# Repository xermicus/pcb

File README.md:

# Schemas and PCB
Shelter for my Schemas and PCB stuff

# LICENSE
This project is licensed under the [Mozilla Public License](LICENSE)

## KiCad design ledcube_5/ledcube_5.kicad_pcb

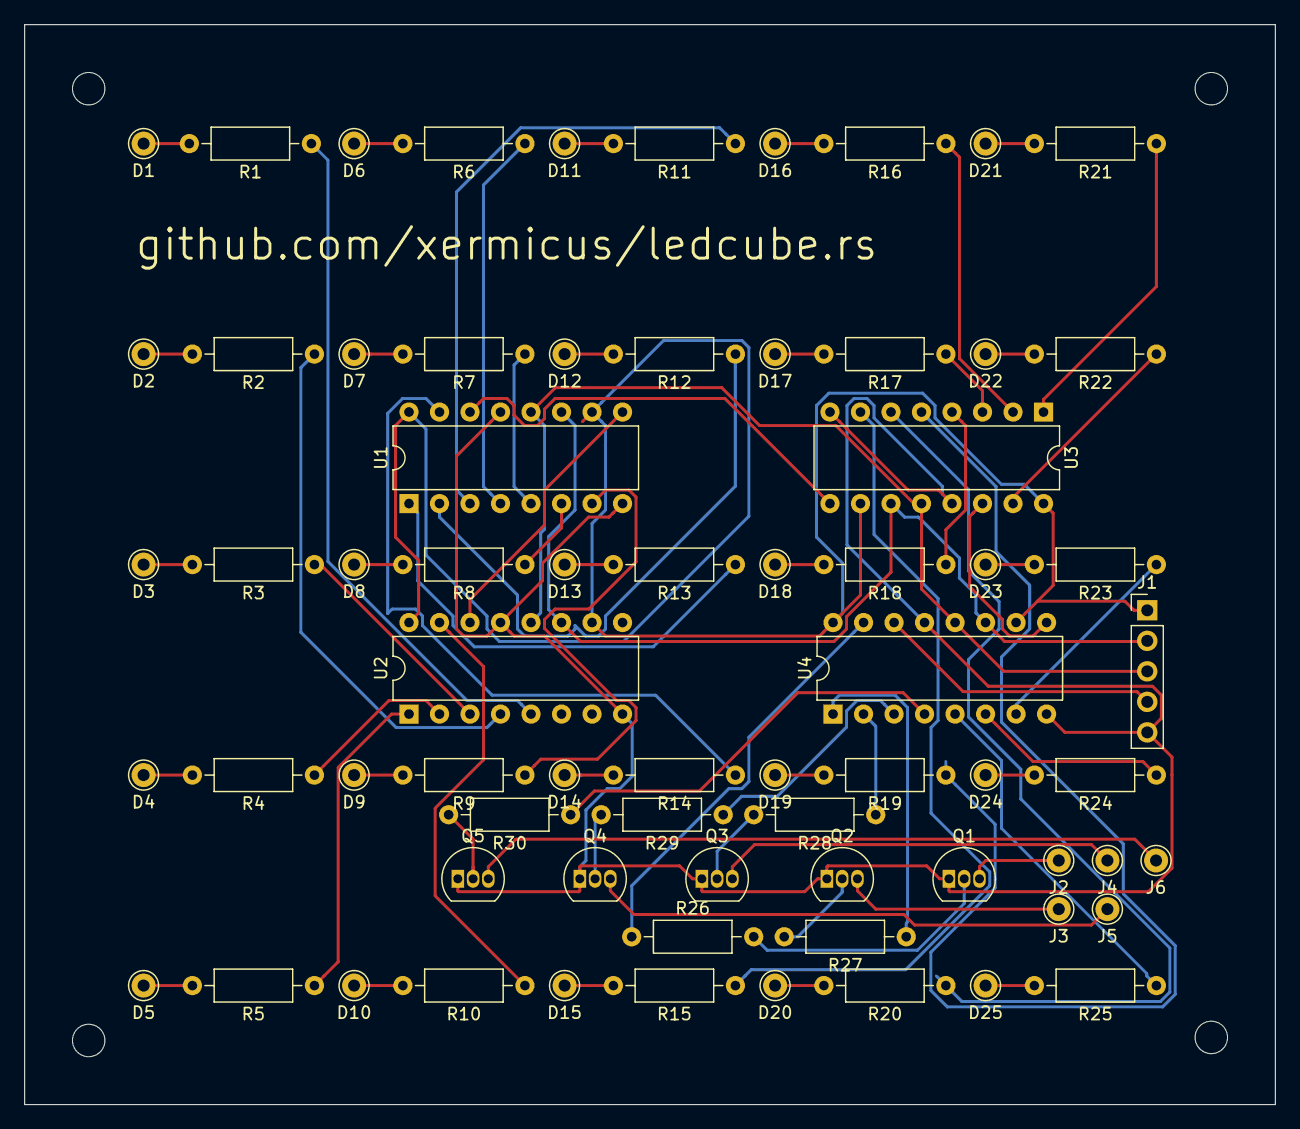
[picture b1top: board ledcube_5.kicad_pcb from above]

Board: 2 copper layers, 104.1 x 89.9 mm, 70 parts (0 on the bottom side), 73 nets.

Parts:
D1, D2, D3, D4, D5, D6, D7, D8, D9, D10, D11, D12, D13, D14, D15, D16, D17, D18, D19, D20, D21, D22, D23, D24, D25: LED; Pin_D1.0mm_L10.0mm
J1: Conn_01x05_MountingPin; PinHeader_1x05_P2.54mm_Vertical
J2, J3, J4, J5, J6: Conn_01x01; Pin_D1.0mm_L10.0mm
Q1, Q2, Q3, Q4, Q5: PN2222A; TO-92_Inline
R1, R2, R3, R4, R5, R6, R7, R8, R9, R10, R11, R12, R13, R14, R15, R16, R17, R18, R19, R20, R21, R22, R23, R24, R25: 100R; R_Axial_DIN0207_L6.3mm_D2.5mm_P10.16mm_Horizontal
R26, R27, R28, R29, R30: 510; R_Axial_DIN0207_L6.3mm_D2.5mm_P10.16mm_Horizontal
U1, U2, U3, U4: 74HC595; DIP-16_W7.62mm

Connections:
+5V: J1.1, U1.10, U1.16, U2.10, U2.16, U3.10, U3.16, U4.10, U4.16
/A0: J1.2, U1.11, U2.11, U3.11, U4.11
/A4: J1.3, U1.12, U2.12, U3.12, U4.12
/A12: J1.4, U4.14
/U1_A: R14.1, U1.15
/U1_B: R13.1, U1.1
/U1_C: R12.1, U1.2
/U1_D: R11.1, U1.3
/U1_E: R6.1, U1.4
/U1_F: R7.1, U1.5
/U1_G: R8.1, U1.6
/U1_H: R9.1, U1.7
/U1_HH: U1.9, U2.14
/U2_A: R10.1, U2.15
/U2_B: R5.1, U2.1
/U2_C: R4.1, U2.2
/U2_D: R3.1, U2.3
/U2_E: R2.1, U2.4
/U2_F: R1.1, U2.5
/U3_A: R22.1, U3.15
/U3_B: R21.1, U3.1
/U3_C: R16.1, U3.2
/U3_D: R17.1, U3.3
/U3_E: R18.1, U3.4
/U3_F: R19.1, U3.5
/U3_G: R20.1, U3.6
/U3_H: R15.1, U3.7
/U3_HH: U1.14, U3.9
/U4_A: R26.1, U4.15
/U4_B: R27.1, U4.1
/U4_C: R28.1, U4.2
/U4_D: R29.1, U4.3
/U4_E: R30.1, U4.4
/U4_F: R25.1, U4.5
/U4_G: R24.1, U4.6
/U4_H: R23.1, U4.7
/U4_HH: U3.14, U4.9
GND: J1.5, Q1.1, Q2.1, Q3.1, Q4.1, Q5.1, U1.8, U1.13, U2.8, U2.13, U3.8, U3.13, U4.8, U4.13
unnamed: D1.1, R1.2
unnamed: D2.1, R2.2
unnamed: D3.1, R3.2
unnamed: D4.1, R4.2
unnamed: D5.1, R5.2
unnamed: D6.1, R6.2
unnamed: D7.1, R7.2
unnamed: D8.1, R8.2
unnamed: D9.1, R9.2
unnamed: D10.1, R10.2
unnamed: D11.1, R11.2
unnamed: D12.1, R12.2
unnamed: D13.1, R13.2
unnamed: D14.1, R14.2
unnamed: D15.1, R15.2
unnamed: D16.1, R16.2
unnamed: D17.1, R17.2
unnamed: D18.1, R18.2
unnamed: D19.1, R19.2
unnamed: D20.1, R20.2
unnamed: D21.1, R21.2
unnamed: D22.1, R22.2
unnamed: D23.1, R23.2
unnamed: D24.1, R24.2
unnamed: D25.1, R25.2
unnamed: J2.1, Q1.3
unnamed: J3.1, Q2.3
unnamed: J4.1, Q3.3
unnamed: J5.1, Q4.3
unnamed: J6.1, Q5.3
unnamed: Q1.2, R26.2
unnamed: Q2.2, R27.2
unnamed: Q3.2, R28.2
unnamed: Q4.2, R29.2
unnamed: Q5.2, R30.2

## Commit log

2021-08-07 begin
2021-08-07 add power source
2021-08-09 ledcube pcb draft
2021-08-09 ledcube pcb tracks
2021-08-10 fix missing R for transistors
2021-08-10 ledcube mounting holes and silkscreen
2021-08-10 ledcube gerber files
2022-01-12 add license
